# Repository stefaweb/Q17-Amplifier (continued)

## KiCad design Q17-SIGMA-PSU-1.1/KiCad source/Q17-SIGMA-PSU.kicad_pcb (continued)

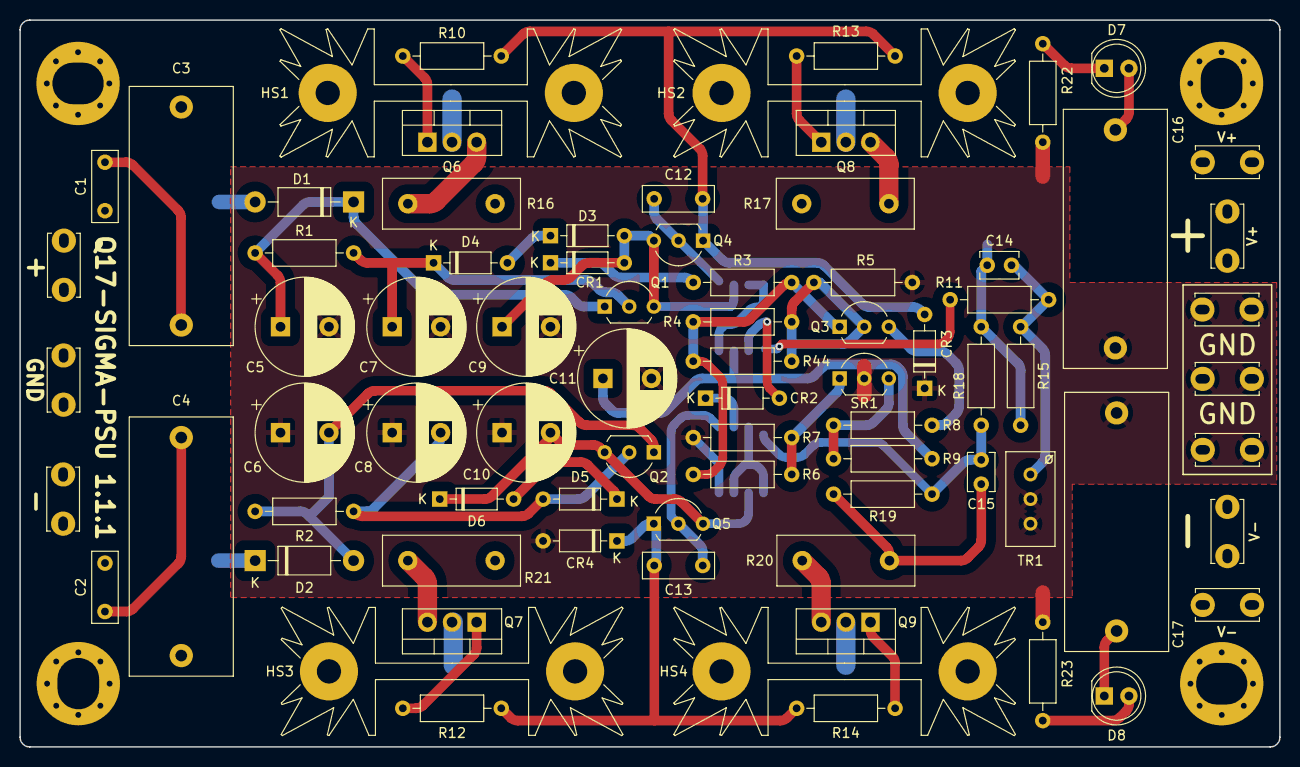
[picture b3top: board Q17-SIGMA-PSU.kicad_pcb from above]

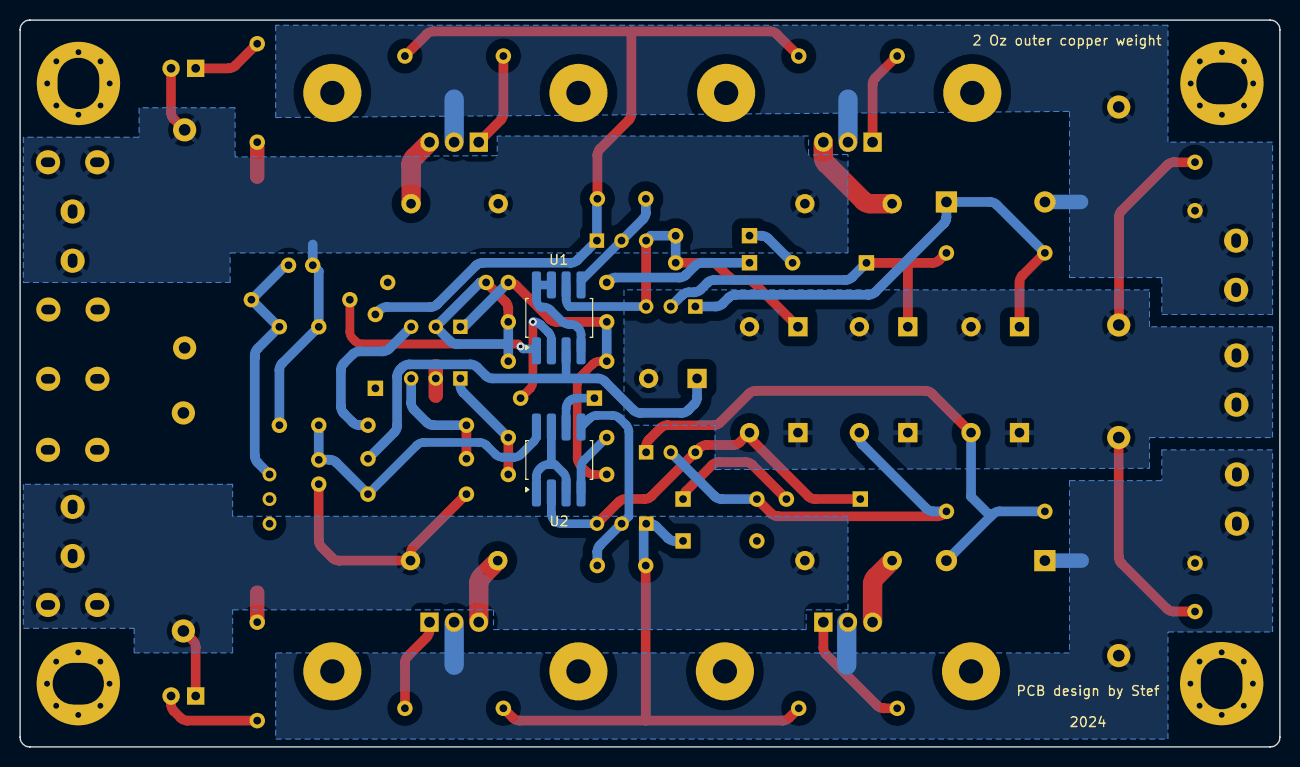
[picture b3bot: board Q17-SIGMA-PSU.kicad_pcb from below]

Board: 2 copper layers, 130.0 x 75.0 mm, 84 parts (2 on the bottom side), 41 nets.

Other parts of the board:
PAD1, PAD2, PAD3, PAD3#2: MountingHole_4.3mm_M4_Pad_Via

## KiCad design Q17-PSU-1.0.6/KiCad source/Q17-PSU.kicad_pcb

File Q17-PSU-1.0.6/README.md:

# Q17-PSU version 1.0.6<br>

Universal Power Supply for Class B amplifiers.

Version 1.0.6 published on October 20, 2023.

<a href="https://audio.cyberkata.org/Q17-PSU-BOM.html">Online Q17-PSU-BOM</a><br>

Classic version with Vishay bridge and Nichicon Muse capacitors (max 63V).

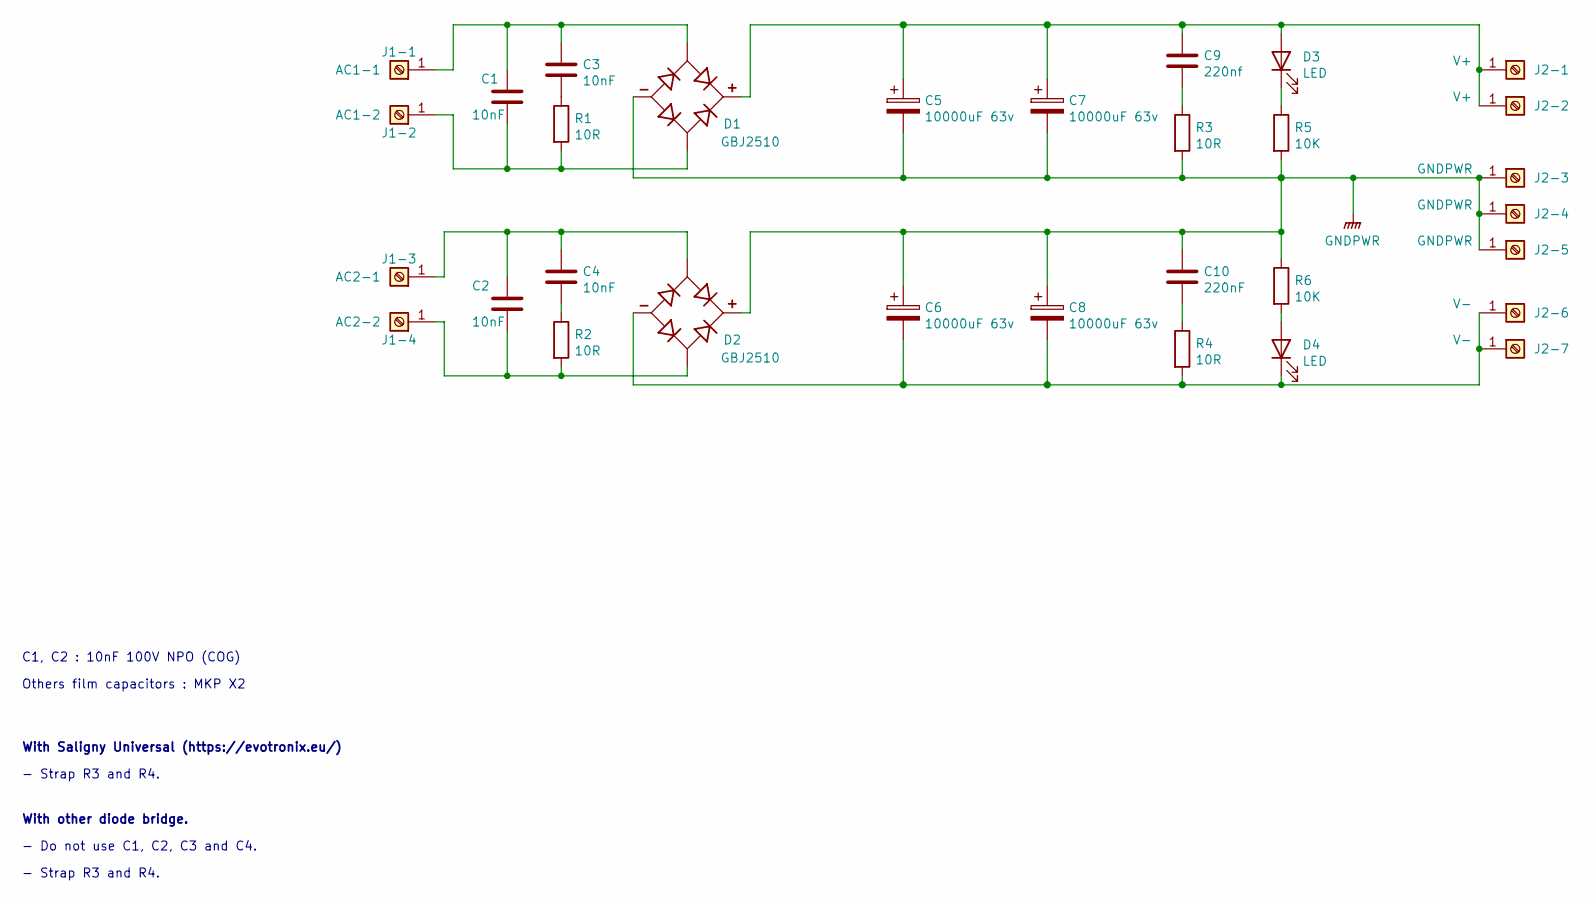
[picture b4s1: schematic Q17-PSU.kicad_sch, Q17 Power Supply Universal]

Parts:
C1, C2: 10nF; C_Disc_D6.0mm_W4.4mm_P5.00mm; Part# FG28C0G2A103JRT06; Mouser 810-FG28C0G2A103JRT6
C3, C4: 10nF; C_Rect_L13.0mm_W5.0mm_P10.00mm_FKS3_FKP3_MKS4; Part# MPX103K305D; Mouser 598-MPX103K305D
C5, C6, C7, C8: 10000uF 63v; CP_Radial_D35.0mm_P10.00mm_SnapIn; Part# 861020786030; Mouser 710-861020786030
C9: 220nf; C_Rect_Q17_PSU_L26.50_H11.00_P20.50; Part# MPX224K305E; Mouser 598-MPX224K305E
C10: 220nF; C_Rect_Q17_PSU_L26.50_H11.00_P20.50; Part# MPX224K305E; Mouser 598-MPX224K305E
D1, D2: GBJ2510; DIOB_GBJ2510; Part# GSIB2580-E3/45; Mouser 625-GSIB2580-E3
D3, D4: LED; LED_D5.0mm; Part# TLHR5400; Mouser 78-TLHR5400
J1-1: AC1-1; Faston_Connector_63849-1_TEC; Part# TE Connectivity 63849-1; Mouser 571-638241
J1-2: AC1-2; Faston_Connector_63849-1_TEC; Part# TE Connectivity 63849-1; Mouser 571-638241
J1-3: AC2-1; Faston_Connector_63849-1_TEC; Part# TE Connectivity 63849-1; Mouser 571-638241
J1-4: AC2-2; Faston_Connector_63849-1_TEC; Part# TE Connectivity 63849-1; Mouser 571-638241
J2-1, J2-2: V+; Faston_Connector_63849-1_TEC; Part# TE Connectivity 63849-1; Mouser 571-638241
J2-3, J2-4, J2-5: GNDPWR; Faston_Connector_63849-1_TEC; Part# TE Connectivity 63849-1; Mouser 571-638241
J2-6, J2-7: V-; Faston_Connector_63849-1_TEC; Part# TE Connectivity 63849-1; Mouser 571-638241
R1, R2, R3, R4: 10R; R_Axial_DIN0207_L6.3mm_D2.5mm_P10.16mm_Horizontal; Part# MRS25000C1009FRP00; Mouser 594-MRS25000C1009FRP
R5, R6: 10K; R_Axial_DIN0207_L6.3mm_D2.5mm_P10.16mm_Horizontal; Part# PR01000101002JR500; Mouser 594-5073NW10K00J

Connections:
GNDPWR: C5.2, C6.1, C7.2, C8.1, C10.1, D1.4, D2.1, J2-3.1, J2-4.1, J2-5.1, R3.2, R5.2, R6.1
unnamed: C3.2, R1.1
unnamed: C4.2, R2.1
unnamed: C9.2, R3.1
unnamed: C10.2, R4.1
unnamed: C5.1, C7.1, C9.1, D1.1, D3.2 (A), J2-1.1, J2-2.1
unnamed: D3.1 (K), R5.1
unnamed: D4.2 (A), R6.2
unnamed: C6.2, C8.2, D2.4, D4.1 (K), J2-6.1, J2-7.1, R4.2
unnamed: C1.1, C3.1, D1.2, J1-1.1
unnamed: C1.2, D1.3, J1-2.1, R1.2
unnamed: C2.1, C4.1, D2.2, J1-3.1
unnamed: C2.2, D2.3, J1-4.1, R2.2

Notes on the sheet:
- Strap R3 and R4.
With Saligny Universal (https://evotronix.eu/)
With other diode bridge.
C1, C2 : 10nF 100V NPO (COG)
- Do not use C1, C2, C3 and C4.
Others film capacitors : MKP X2

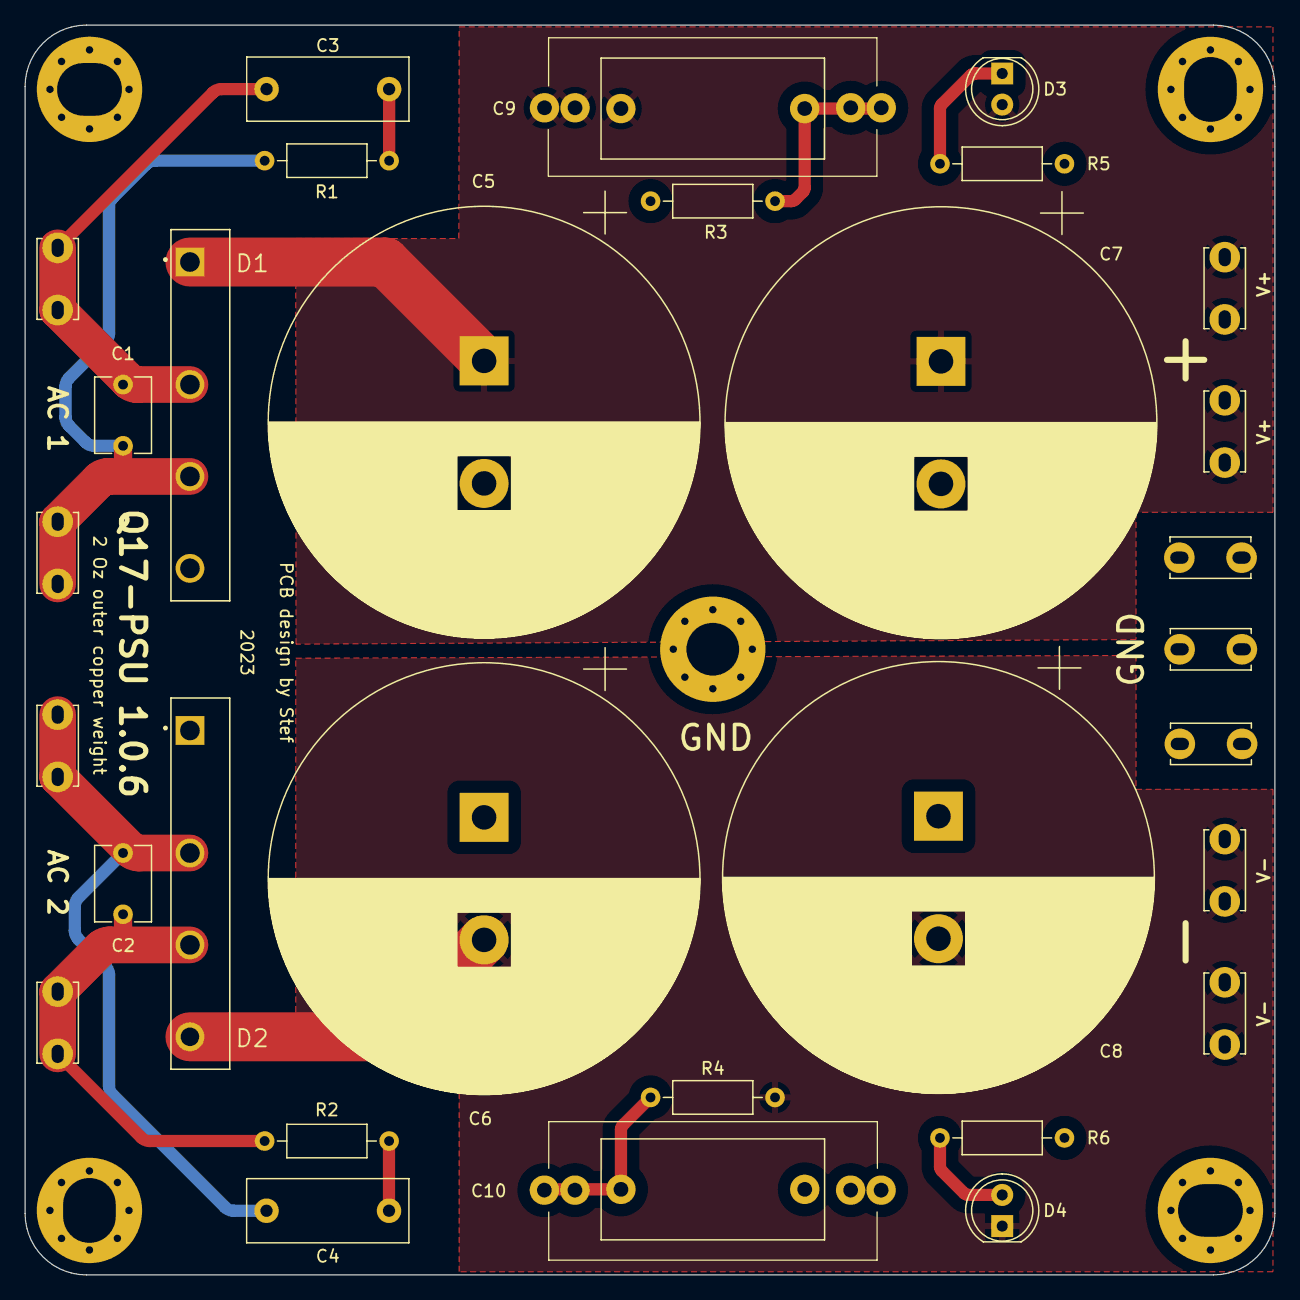
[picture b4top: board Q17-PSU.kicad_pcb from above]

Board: 2 copper layers, 102.0 x 102.0 mm, 31 parts (0 on the bottom side), 13 nets.

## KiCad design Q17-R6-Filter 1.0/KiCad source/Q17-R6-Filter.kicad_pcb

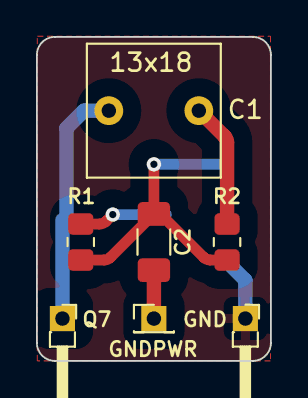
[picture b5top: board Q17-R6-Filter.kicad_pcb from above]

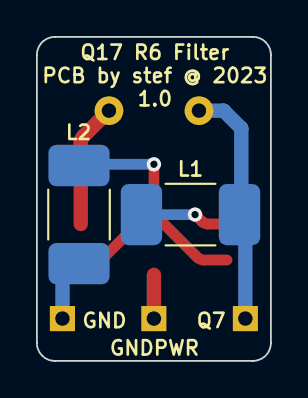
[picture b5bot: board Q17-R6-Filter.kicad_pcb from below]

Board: 2 copper layers, 13.0 x 18.0 mm, 9 parts (2 on the bottom side), 6 nets.

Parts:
C1: 22nF; C_Rect_L7.2mm_W7.2mm_P5.00mm_FKS2_FKP2_MKS2_MKP2
C2: 470pF; C_1206_3216Metric_Pad1.33x1.80mm_HandSolder
J1: R6(Q7); PinHeader_1x01_P1.27mm_Horizontal
J2: R6(GND); PinHeader_1x01_P1.27mm_Horizontal
J3: GNDPWR(R32); PinHeader_1x01_P1.27mm_Vertical
L1, L2: 4.7uH; L_1812_4532Metric_Pad1.30x3.40mm_HandSolder
R1: 100R; R_0805_2012Metric_Pad1.20x1.40mm_HandSolder
R2: 220R; R_0805_2012Metric_Pad1.20x1.40mm_HandSolder

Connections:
GND: J2.1, L2.2
GNDPWR: C2.2, J3.1
unnamed: C1.2, R2.1
unnamed: C2.1, L2.1, R1.2, R2.2
unnamed: C1.1, J1.1, L1.1
unnamed: L1.2, R1.1

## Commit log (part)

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2023-10-05 Q17-Mini 1.3.1 files archived
2023-10-20 Q17-PSU 1.0.6
2023-10-20 Added new Q17-PSU measures for Saligny bridges
2024-01-06 Q17-Mini-schematic 2.0.3 with measures
2024-04-14 First upload
2024-04-14 Upload sigma pictures.
2024-04-15 Q17-PSU-MONO first upload
2024-04-15 Q17-PSU-MONO-SCHEMATIC update
2024-04-15 Update Gerber files (missing drill)
2024-04-15 Q17-SIGMA-PSU-schematic update
2024-04-15 Update Q17-SIGMA-PSU diagram
2024-04-17 Q17-SIGMA-PSU-schematic
2024-04-22 Q17-SIGMA-PSU 1.1 update
2024-04-22 Update silkscreen for U1/U2
2024-04-23 Temporary delete files.
2024-04-24 Update 3D files
2024-04-26 Update files for Q17-SIGMA-PSU
2024-04-26 Dellte wrong files
2024-04-27 Update Q17-SIGMA-PSU-LTSpice
2024-04-28 Update LTSpice sim
2024-04-30 Q17-Mini-LTspice 2.1
2024-04-30 Update Q17-Mini diagram (C7 parts)
2024-05-01 Update Q17-Sigma-psu to 1.1.1 final
2024-05-01 Update LTSpice models and sim
2024-05-01 Rename directory
2024-05-02 Measures for Sigma
2024-05-04 Update diagram
2024-05-05 Update sigma diagram with real measures
2024-05-06 Update R33 to 10R
2024-05-12 Update spectrum
2024-05-21 More updates
2024-05-27 Update Q17-Mini diagram and measures
2024-05-27 Update Q17-Turbo diagram
2024-05-28 Update Q17-Mini diagram
2024-05-28 Update some wrong files
2024-06-08 Q17-Mini 2.2.1 upload
    Version 2.0 archived in "Q17-Mini Archives".
2024-06-14 Update Q17-Mini measures
2024-06-22 Update LTSpice files
2024-06-25 Added some measures for Q17 2.2
2024-06-25 Update some measures
2024-07-01 Upload Q17-Mini 3.0
    First upload
2024-07-02 Archive Q17-Mini 2.2
2024-07-09 Update Q17-Mini 3.0 diagram
2024-07-22 Update power transistor selection table
2024-07-22 Update Q17 Transistor table
2024-07-27 Update Q17-MIni diagram (R15=150R)
2024-07-27 Update Q17-Mini 2.3.7 spice model
2024-08-04 Update spice models
2024-08-07 Update Q17-Mini 2.3.8 spice model
2024-08-07 Update Q17-Mini 1.6 spice model
2024-08-08 Removed old PSU project.
2024-08-08 Updated PSU PCB.
2024-08-08 New upload
2024-08-09 Upload Q17-PSU 1.1
2024-08-09 Remove old PSU version.
2024-08-10 Update Q17-Power-Transistors-Selection-1.4.4 (added config D4)
2024-08-20 Update Q17-Turbo measures
2024-08-21 Update Q17-Turbo files
2024-08-23 Upload Q17-Mini 3.0.2
2024-08-26 Update Q17-Mini-schematic
2024-09-10 Updated Q17-Power-Transistors-Selection-1.5.1
2024-09-12 Update preview Q17-Turbo 2.0
    Update preview Q17-Turbo 2.0
2024-09-27 Fixing Plate-Q17-Turbo-216x80-1.0
2024-09-27 Mounting Plate-Q17-Turbo-216x80-1.0
2024-10-09 Update Q17-Mini 3.0 measures
2024-12-16 Removed PSU files.
